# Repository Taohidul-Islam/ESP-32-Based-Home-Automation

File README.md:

# ESP-32-Based-Home-Automation
<h2>This Board can turn any regular household electric switchboard into a smart Wi-Fi and Remote controlled switchboard.</h2>
<p>Here the board I designed is fail protected, meaning even if my electronic logic fails, the switchboard would work like a regular switchboard. The Automation Board is designed maintaining hierarchy. Meaning the Automation Board can only work only if the main switch from switch board is set to "on". In my logic I don't really turn anything "On". Everything is default "On" and "Off" by switchboard. I can just turn the things "Off" when the switch is "On" by triggering relay and turn the things back to it's default "On" position</p>
<p>N.B. IR remote control is currently unavailable and AC induction fan control channel can be faulty as it is not tested(will test soon).</p>

<P>Here are some screenshots of my PCB And Schematics</P>

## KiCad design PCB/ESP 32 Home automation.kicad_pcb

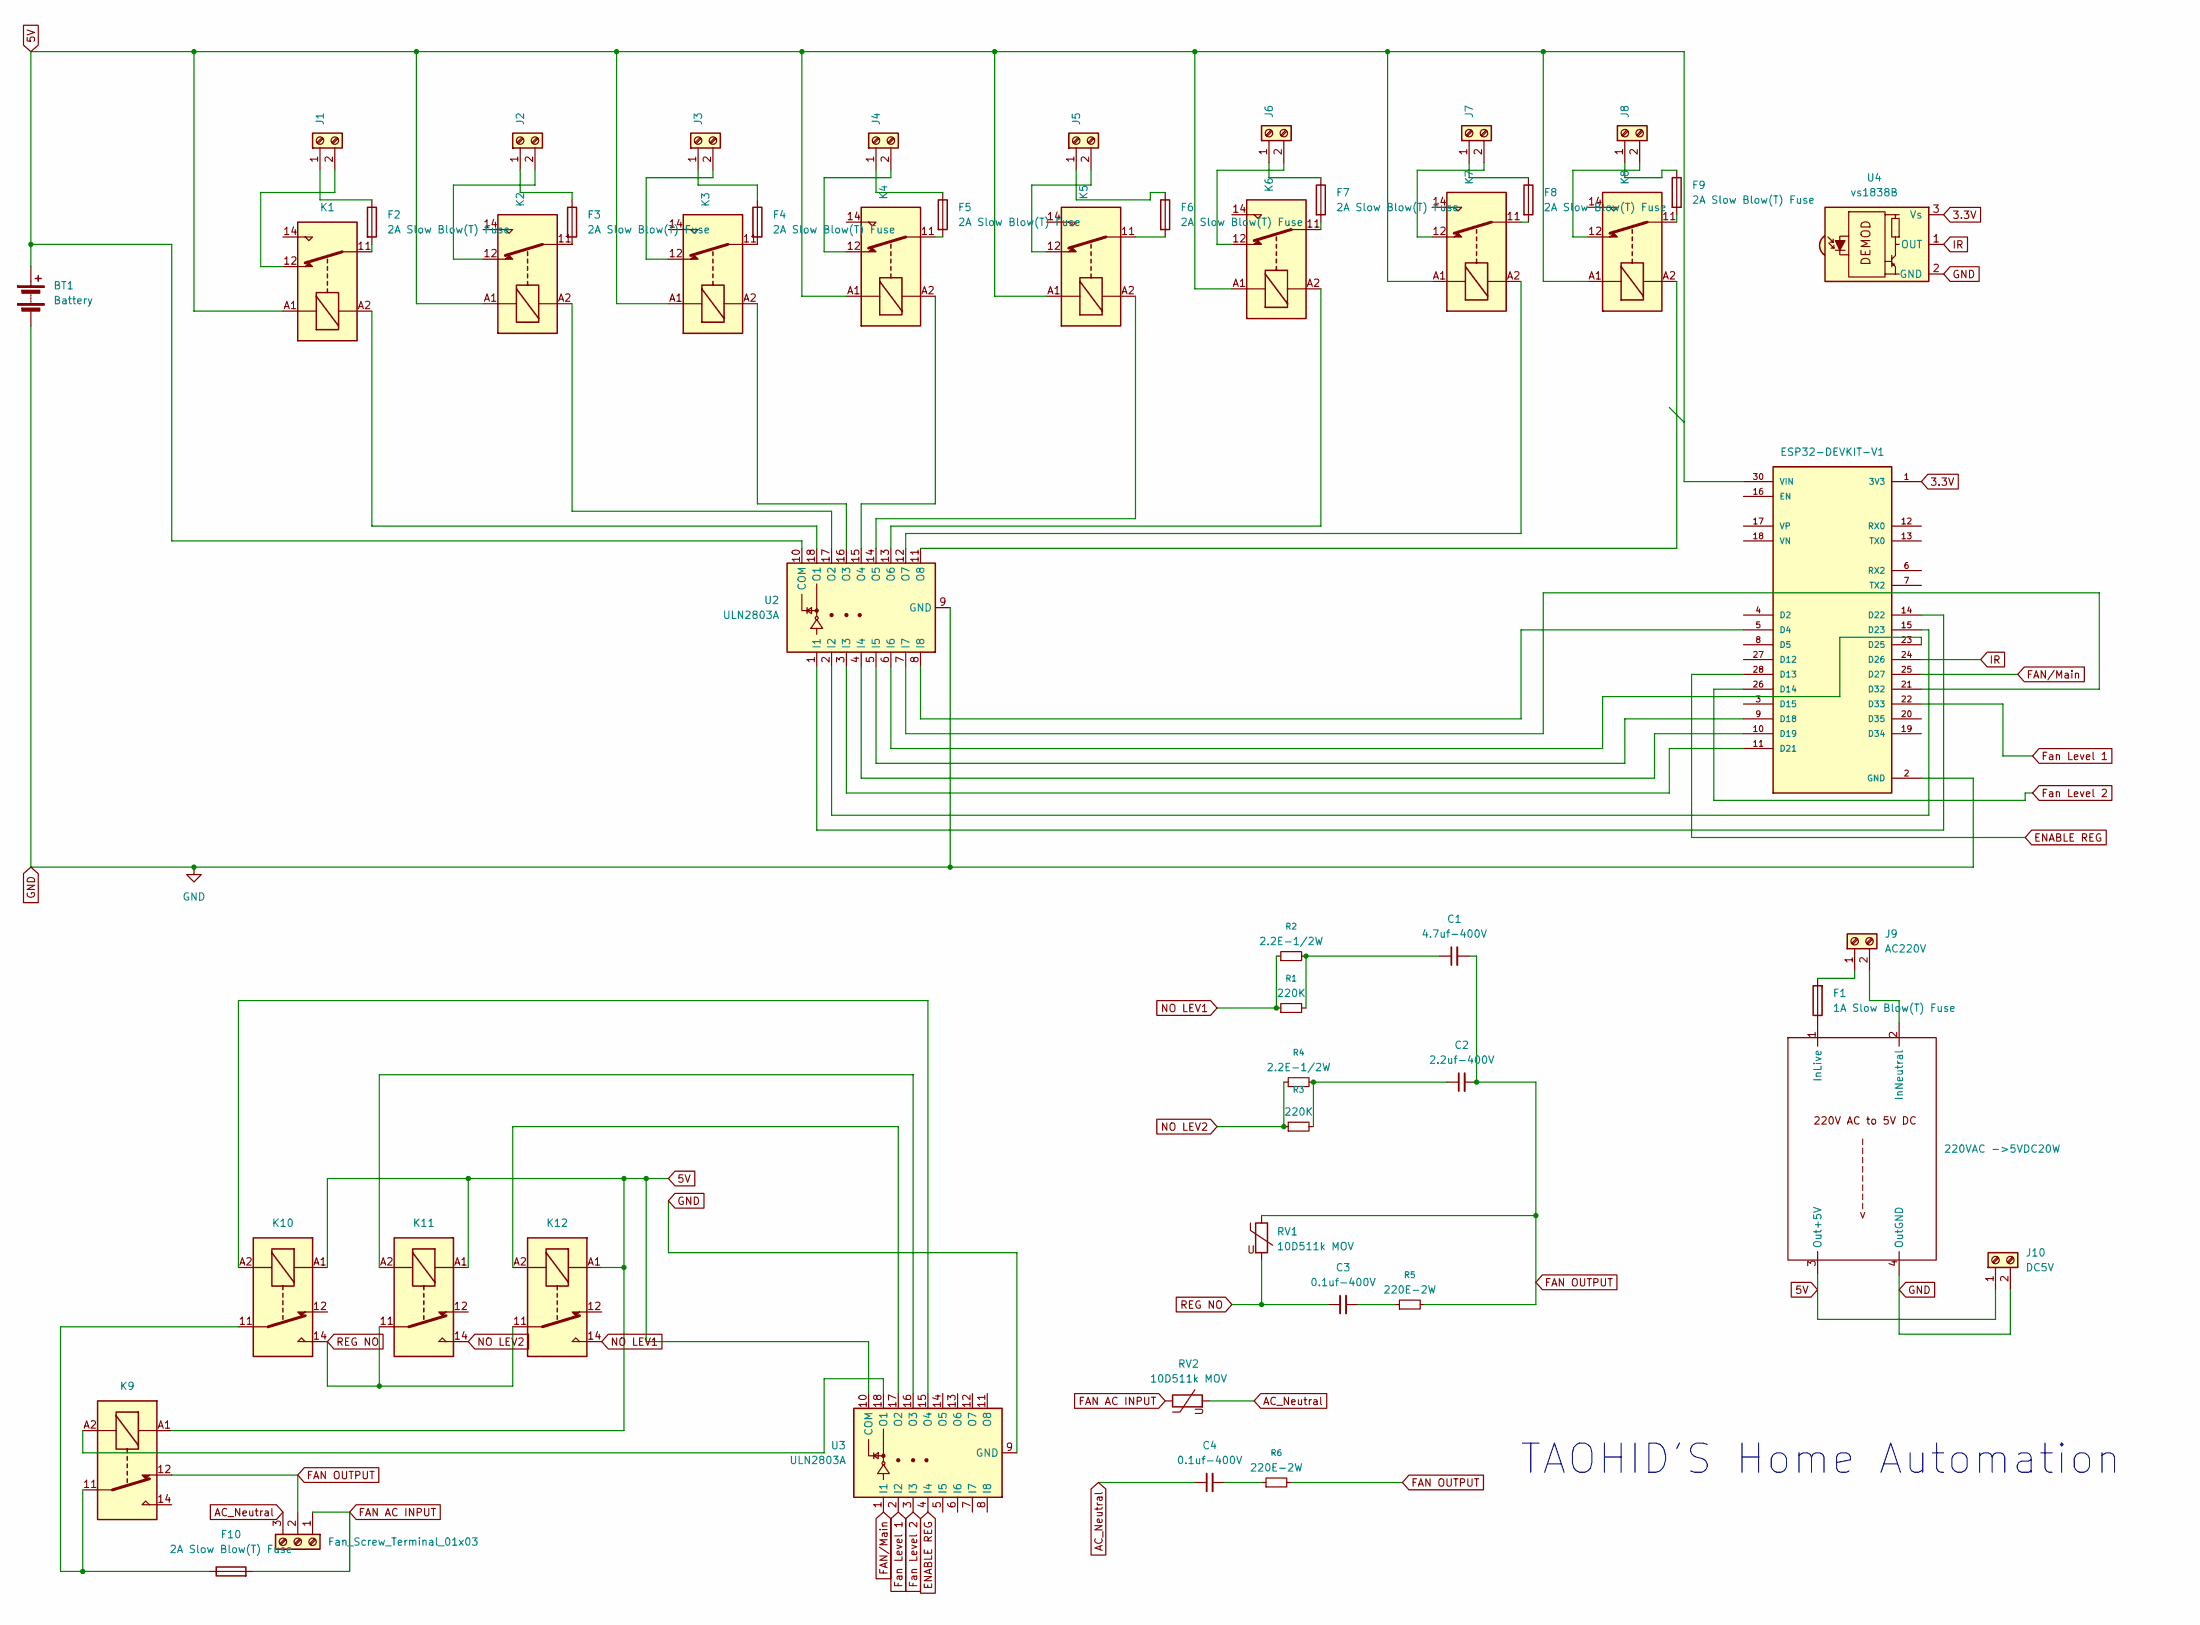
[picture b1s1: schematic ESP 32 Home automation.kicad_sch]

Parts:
Adapter/Charger1: 220VAC ->5VDC20W; ACtoDC power Adapter. 220V to 5V
BT1: Battery; TerminalBlock_MaiXu_MX126-5.0-02P_1x02_P5.00mm
C1: 4.7uf-400V; C_Rect_L32.0mm_W15.0mm_P27.00mm
C2: 2.2uf-400V; C_Rect_L27.0mm_W9.0mm_P22.00mm
C3, C4: 0.1uf-400V; C_Rect_L13.0mm_W6.5mm_P7.50mm_P10.00mm
F1: 1A Slow Blow(T) Fuse; Fuseholder_Littelfuse_100_series_5x20mm
F2, F3, F4, F5, F6, F7, F8, F9, F10: 2A Slow Blow(T) Fuse; Fuseholder_Littelfuse_100_series_5x20mm
J1, J2, J3, J4, J5, J6, J7, J8: Screw_Terminal_01x02; TerminalBlock_Phoenix_MKDS-1,5-2-5.08_1x02_P5.08mm_Horizont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
J9: AC220V; TerminalBlock_Phoenix_MKDS-1,5-2-5.08_1x02_P5.08mm_Horizont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
J10: DC5V; TerminalBlock_Phoenix_MKDS-1,5-2-5.08_1x02_P5.08mm_Horizont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
J11: Fan_Screw_Terminal_01x03; TerminalBlock_Phoenix_MKDS-1,5-3-5.08_1x03_P5.08mm_Horizont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
K1, K2, K3, K4, K5, K6, K7, K8, K9, K10, K11, K12: JQC-3FF-005-1Z; Relay_SPDT_Hongfa_JQC-3FF_0XX-1Z
R1, R3: 220K; R_Axial_DIN0309_L9.0mm_D3.2mm_P20.32mm_Horizontal
R2, R4: 2.2E-1/2W; R_Axial_DIN0309_L9.0mm_D3.2mm_P20.32mm_Horizontal
R5, R6: 220E-2W; R_Axial_DIN0309_L9.0mm_D3.2mm_P20.32mm_Horizontal
RV1, RV2: 10D511k MOV; RV_Disc_D12mm_W7.5mm_P7.5mm
U1: ESP32-DEVKIT-V1; MODULE_ESP32_DEVKIT_V1; PARTREV N/A
U2, U3: ULN2803A; DIP-18_W7.62mm_Socket_LongPads
U4: vs1838B; Vishay_MOLD-3Pin

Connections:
3.3V: U1.1 (3V3), U4.3 (Vs)
5V: Adapter/Charger1.3 (Out+5V), BT1.1 (+), J10.1, K1.A1, K2.A1, K3.A1, K4.A1, K5.A1, K6.A1, K7.A1, K8.A1, K9.A1, K10.A1, K11.A1, K12.A1, U1.30 (VIN), U2.10 (COM), U3.10 (COM)
AC_Neutral: C4.1, J11.3, RV2.2
ENABLE REG: U1.28 (D13), U3.4 (I4)
FAN AC INPUT: F10.2, J11.1, RV2.1
FAN OUTPUT: C1.2, C2.2, J11.2, K9.12, R5.2, R6.2, RV1.1
FAN/Main: U1.25 (D27), U3.1 (I1)
Fan Level 1: U1.22 (D33), U3.2 (I2)
Fan Level 2: U1.26 (D14), U3.3 (I3)
GND: Adapter/Charger1.4 (OutGND), BT1.2 (-), J10.2, U1.2 (GND), U1.29 (GND), U2.9 (GND), U3.9 (GND), U4.2 (GND)
IR: U1.24 (D26), U4.1 (OUT)
NO LEV1: K12.14, R1.1, R2.1
NO LEV2: K11.14, R3.1, R4.1
unnamed: Adapter/Charger1.1 (InLive), F1.1
unnamed: Adapter/Charger1.2 (InNeutral), J9.2
unnamed: C1.1, R1.2, R2.2
unnamed: C2.1, R3.2, R4.2
unnamed: C3.2, R5.1
unnamed: C4.2, R6.1
unnamed: F2.2, K1.11
unnamed: F3.2, K2.11
unnamed: F4.2, K3.11
unnamed: F5.2, K4.11
unnamed: F6.2, K5.11
unnamed: F7.2, K6.11
unnamed: F8.2, K7.11
unnamed: F9.2, K8.11
unnamed: F10.1, K9.11, K10.11
unnamed: F2.1, J1.1
unnamed: J1.2, K1.12
unnamed: F3.1, J2.1
unnamed: J2.2, K2.12
unnamed: F4.1, J3.1
unnamed: J3.2, K3.12
unnamed: F5.1, J4.1
unnamed: J4.2, K4.12
unnamed: F6.1, J5.1
unnamed: J5.2, K5.12
unnamed: F7.1, J6.1
unnamed: J6.2, K6.12
unnamed: F8.1, J7.1
unnamed: J7.2, K7.12
unnamed: F9.1, J8.1
unnamed: J8.2, K8.12
unnamed: F1.2, J9.1
unnamed: U1.5 (D4), U2.8 (I8)
unnamed: U1.9 (D18), U2.5 (I5)
unnamed: U1.10 (D19), U2.4 (I4)
unnamed: U1.11 (D21), U2.3 (I3)
unnamed: U1.14 (D22), U2.1 (I1)
unnamed: U1.15 (D23), U2.2 (I2)
unnamed: U1.23 (D25), U2.6 (I6)
unnamed: U1.21 (D32), U2.7 (I7)
unnamed: K1.A2, U2.18 (O1)
unnamed: K2.A2, U2.17 (O2)
unnamed: K3.A2, U2.16 (O3)
unnamed: K4.A2, U2.15 (O4)
unnamed: K5.A2, U2.14 (O5)
unnamed: K6.A2, U2.13 (O6)
unnamed: K7.A2, U2.12 (O7)
unnamed: K8.A2, U2.11 (O8)
unnamed: K9.A2, U3.18 (O1)
unnamed: K12.A2, U3.17 (O2)
unnamed: K11.A2, U3.16 (O3)
unnamed: K10.A2, U3.15 (O4)
REG NO: C3.1, K10.14, K11.11, K12.11, RV1.2

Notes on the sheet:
TAOHID'S Home Automation

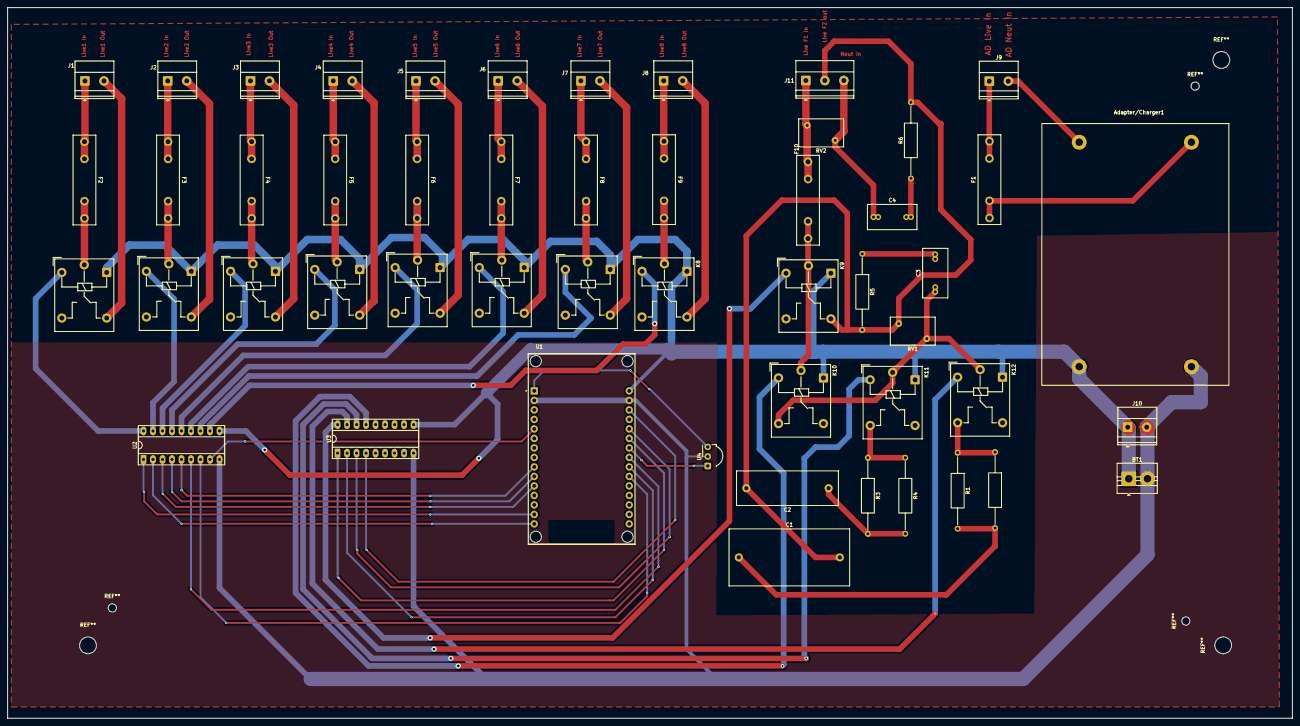
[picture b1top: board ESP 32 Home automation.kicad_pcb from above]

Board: 2 copper layers, 343.5 x 190.0 mm, 51 parts (0 on the bottom side), 66 nets.

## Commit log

2025-12-23 Revise IR remote note and add caution for fan control
    Updated the note about IR remote control and added a caution regarding the AC induction fan control channel.
2025-12-24 Create PCB
2025-12-26 Revise BOM.csv with new product entries and fixes
    Updated BOM.csv to include additional product details and corrected formatting issues.
